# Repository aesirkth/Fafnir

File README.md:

# Fafnir
Propulsion Engine Controller

# Prerequisites
Follow [zephyr getting started guide](https://docs.zephyrproject.org/latest/develop/getting_started/index.html)

# Build 

```bash
cd zephyr-firmware
west update
cd fafnir
west build -b fafnir app --pristine
west flash
```

# Build for native simulation
```bash
docker run -ti -v /Volumes/external/zephyrproject/:/workdir -v /Volumes/external/aesir/Fafnir/zephyr-firmware/:/app ghcr.io/zephyrproject-rtos/zephyr-build:main
cd /app/fafnir
west build -b native_sim/native/64 app --pristine -- -DEXTRA_CONF_FILE=debug.conf
./build/zephyr/zephyr.exe
```
or
```bash
west build -b native_sim/native/64 app -- -DEXTRA_CONF_FILE=debug.conf && ./build/zephyr/zephyr.exe
```

## Using shell in simulation

You can send can messages like this
```bash
uart: ~$ can send can_loopback0 ID DATA
```

For example, running
```bash
uart: ~$ can send can_loopback0 123 0
```
will tell Fafnir to go into state STATE_INIT.

Running 
```bash
uart: ~$ can send can_loopback0 124 0 1
```
will use the override feature to set N2 Valve HIGH.

# CAN message specification to Fafnir

| CAN ID | byte | data                         | type  |
| ------ | ---- | ---------------------------- | ----- |
| 0x123  | 0    | launch sequence number (1-6) | uint8 | (setting states mode)
| 0x124  | 0    | Solenoid ID (1-4)            | uint8 | (override mode)
|        | 1    | 1 == open, 0 == closed       | bool  |

Note that the launch sequence number corresponds to the launch sequence number as given in https://aesir.slab.com/posts/mjollnir-launch-sequence-2juh5ekp

Note that the Solenoid ID corresponds to the solenoid ports on the Fafnir board.
Mjollnir only has two solenoids which correspond to:
```
Solenoid ID 2 => Bypass valve
Solenoid ID 3 => Pilot valve
Solenoid ID 4 => Control vent
```
Solenoid IDs 1 and 4 are not connected and don't do anything.

## CAN acknowledges

| CAN ID | byte | data | meaning |
| ------ | ---- | ------  | -----|
| 0x125  | 0   | 0x01    | Changing state! |
|        | 1   |  \<byte\> |  the state we're changing to |
| 0x125  | 0   | 0x02    | Received valid override command! |
|        | 1   | \<byte\> | The first byte we received  |
|        | 2   |  \<byte\> | The second byte we received  |
| 0x125  | 0   | 0xF0    | Recieved invalid state |
| 0x125  | 0   | 0xF1    | Cannot perform ignition command while attempting ignition. (Protection against double send) |
|  | 1   | \<byte\>    | State command we received |
| 0x125  | 0   | 0xF2    | Invalid state command |
| 0x125  | 0   | 0xF3    | Invalid override command |
| 0x125  | 0   | 0xF4    | Invalid pin given in override command |

The state we're changing to is of type equal to this C `enum`:
```c
typedef enum {
    STATE_IDLE,
    STATE_INIT,
    STATE_FILL,
    STATE_STOP_FILL,
    STATE_UMBILICAL,
    STATE_N2_PRESSURIZATION,
    STATE_IGNITION_1,
    STATE_IGNITION_2,
    STATE_IGNITION_3,
    STATE_IGNITION_4,
    STATE_SAFE,
    STATE_ABORT_BEFORE_COUNTDOWN,
    STATE_ABORT_AFTER_COUNTDOWN
} State_t;
```

Note that this is **NOT** the same as the launch sequence number used in the command above (0x123).

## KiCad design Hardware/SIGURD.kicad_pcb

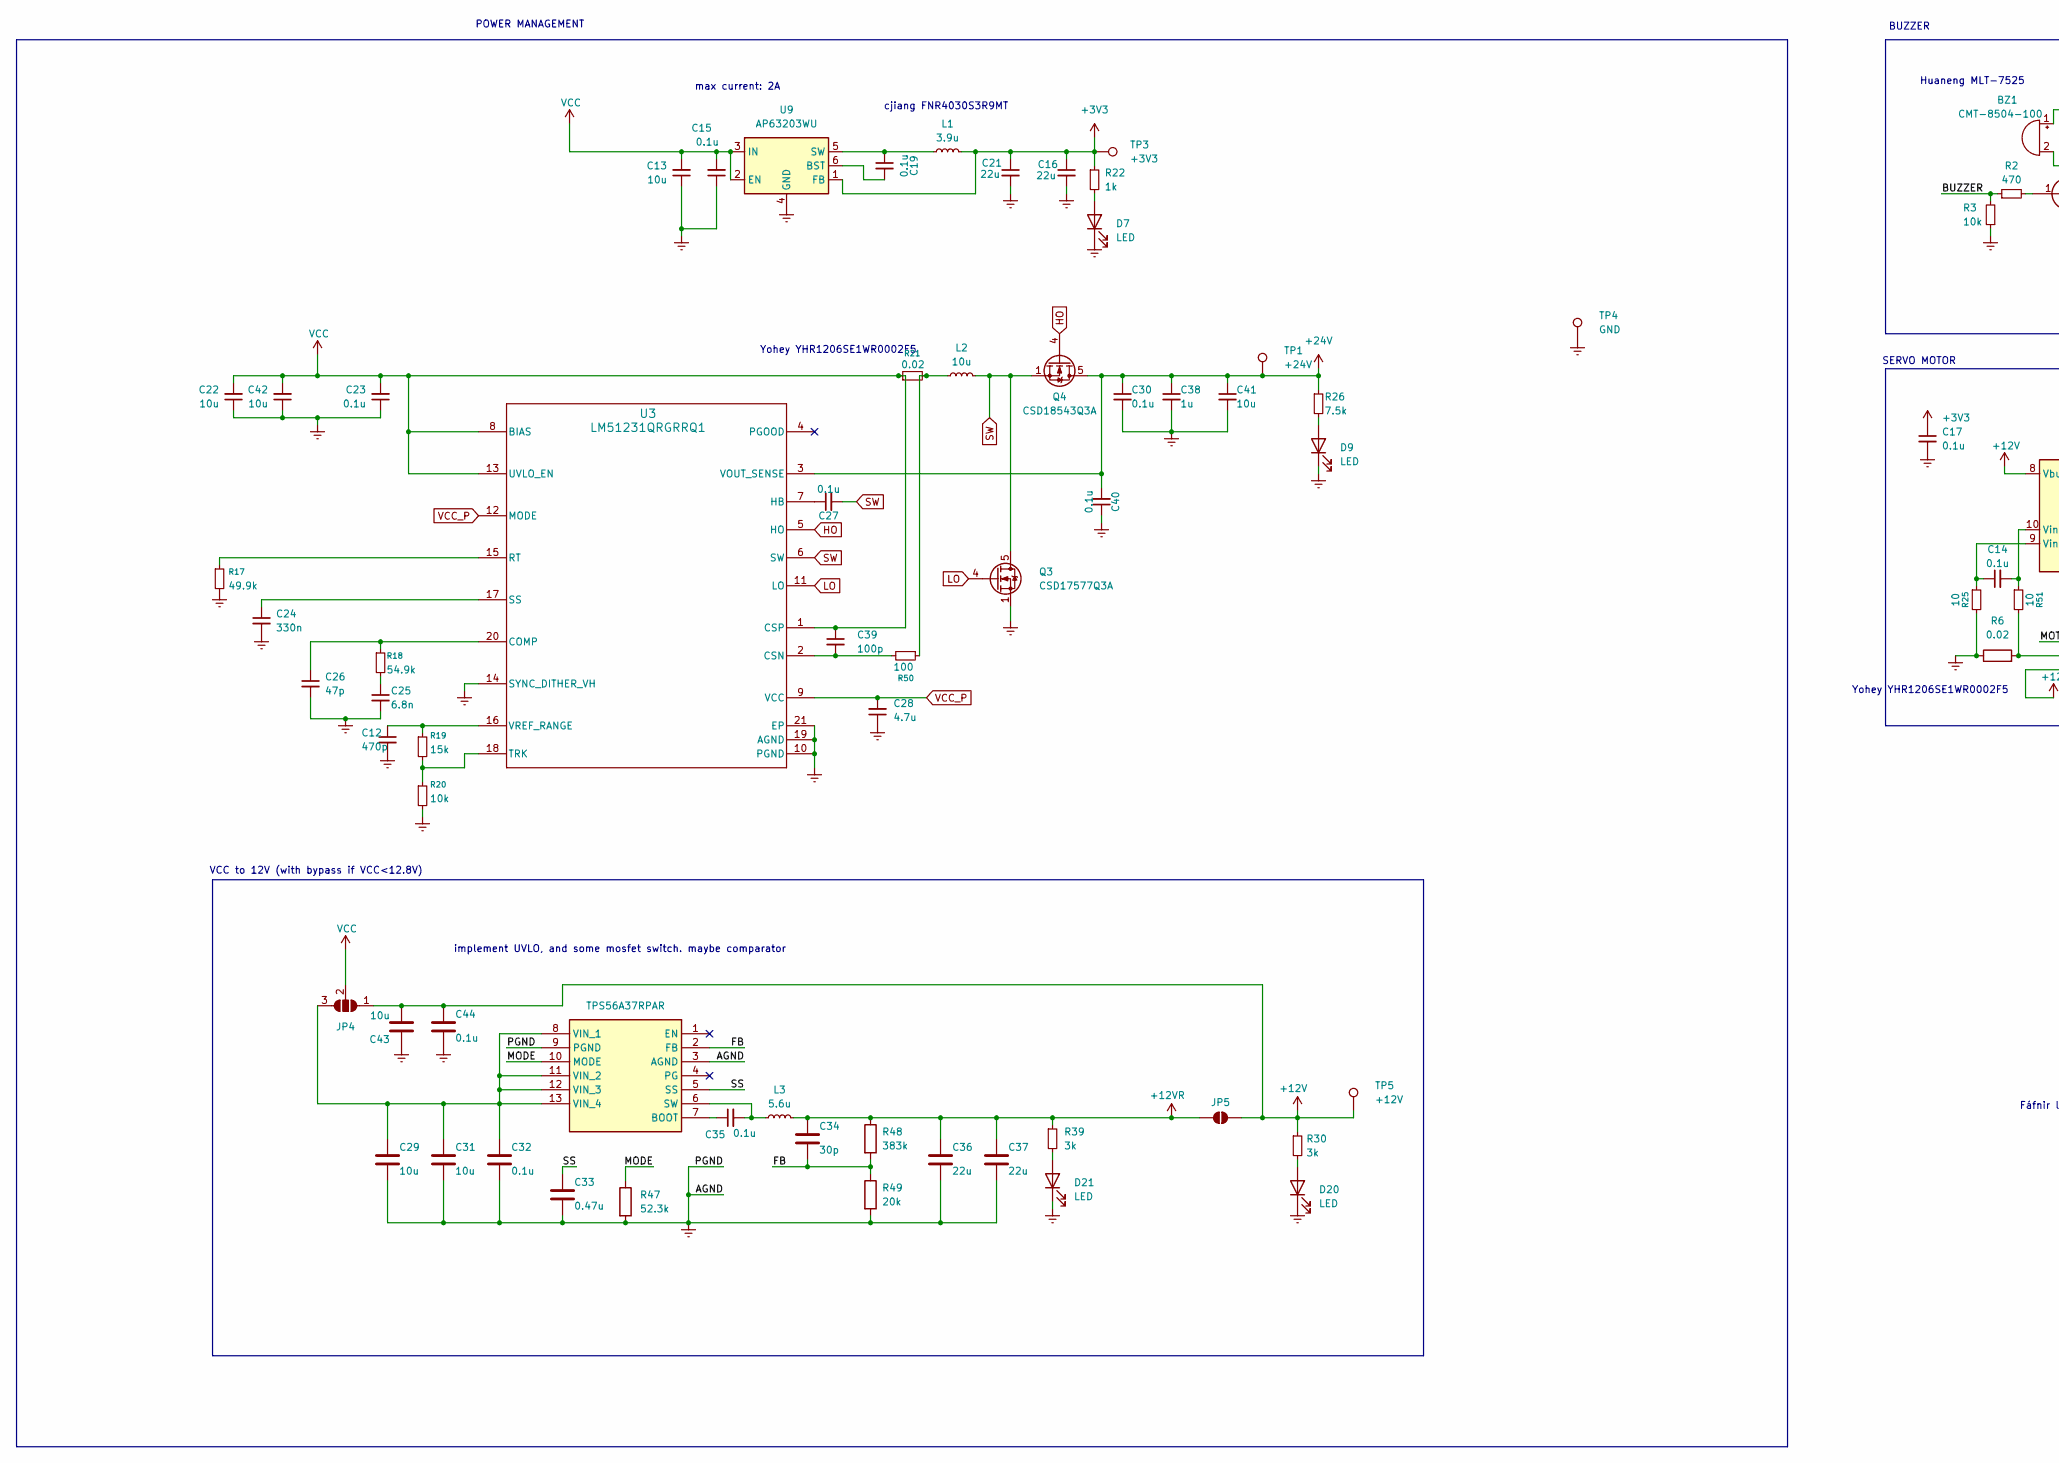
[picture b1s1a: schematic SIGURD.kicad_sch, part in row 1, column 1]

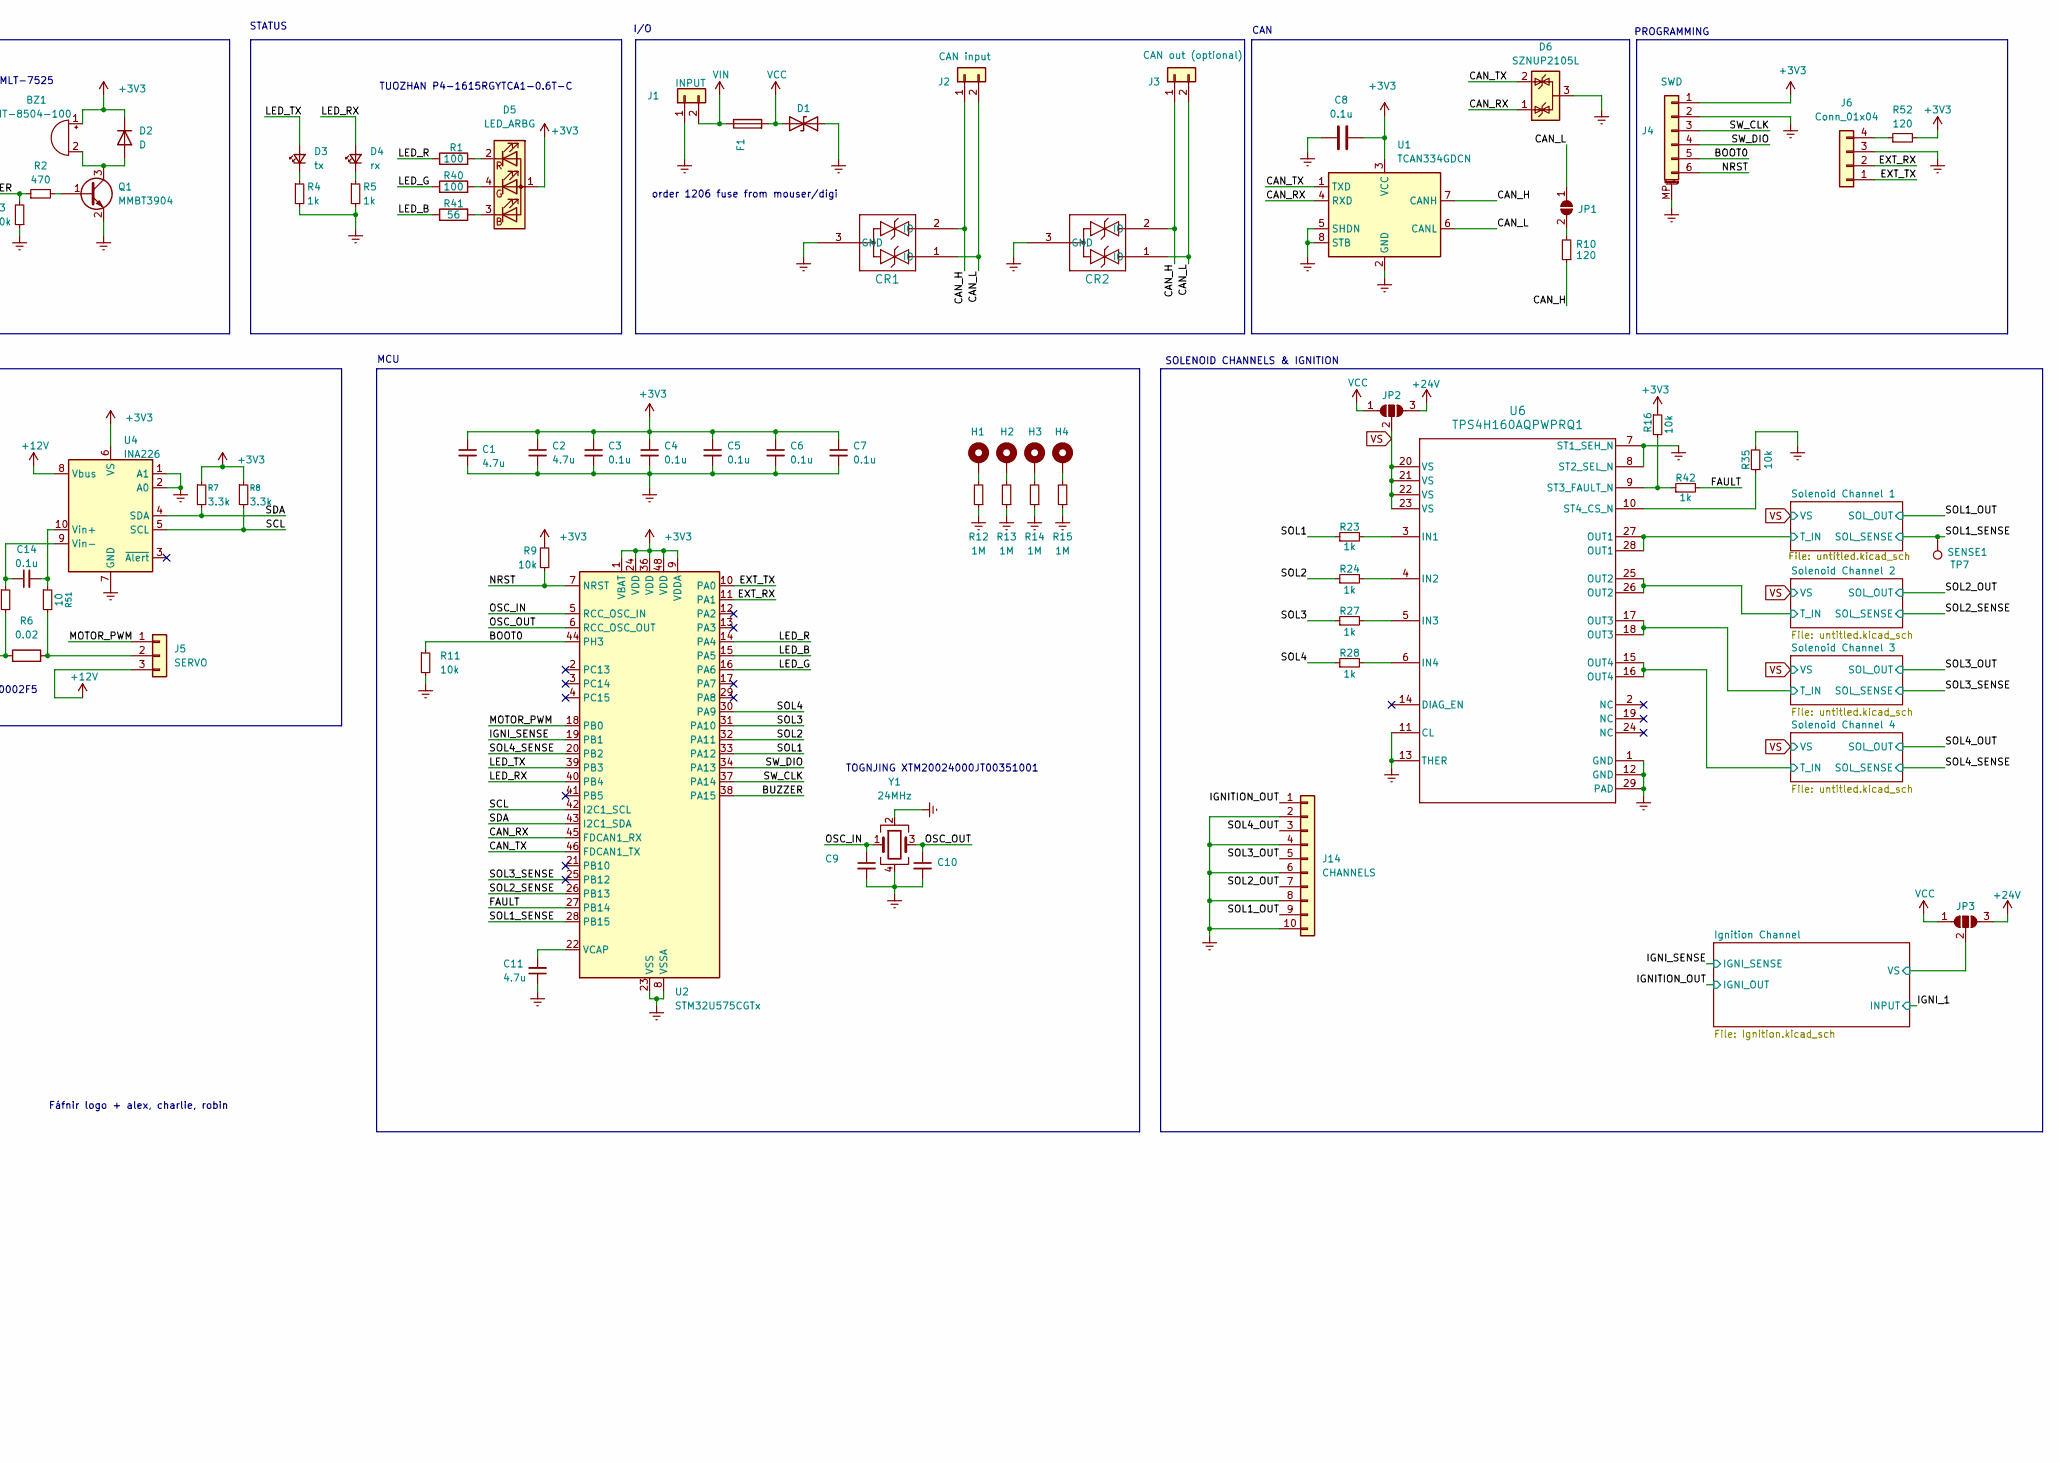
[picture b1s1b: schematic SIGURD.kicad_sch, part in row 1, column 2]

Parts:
BZ1: CMT-8504-100; BUZ-SMD_4P-L7.5-W7.5-P7.59-TL
C1, C2, C11, C28: 4.7u; C_0402_1005Metric
C3, C4, C5, C6, C7, C8, C14, C15, C17, C19, C23, C27, C30, C32, C35, C40, C44: 0.1u; C_0402_1005Metric
C9, C10: 18p; C_0402_1005Metric
C12: 470p; C_0402_1005Metric
C13, C22, C41, C42: 10u; C_0603_1608Metric
C16, C21: 22u; C_0603_1608Metric
C24: 330n; C_0402_1005Metric
C25: 6.8n; C_0402_1005Metric
C26: 47p; C_0402_1005Metric
C29, C31, C43: 10u; C_0805_2012Metric
C33: 0.47u; C_0402_1005Metric
C34: 30p; C_0402_1005Metric
C36, C37: 22u; C_0805_2012Metric
C38: 1u; C_0603_1608Metric
C39: 100p; C_0402_1005Metric
CR1, CR2: ESD2CAN36DBZRQ1; SOT-23-3_DBZ_TEX
D1: D_SOD-123
D2: D; D_SOD-523
D3: tx; D_0603_1608Metric
D4: rx; D_0603_1608Metric
D5: LED_ARBG; LED_Lumex_SML-LX0404SIUPGUSB
D6: SZNUP2105L; SOT-23
D7, D9, D20, D21: LED; D_0603_1608Metric
F1: 15A; Fuse_1206_3216Metric
H1, H2, H3, H4: MountingHole_Pad; MountingHole_3.2mm_M3_Pad_Via
IC3: TPS56A37RPAR; RPA0010A-MFG; Mouser Part Number 595-TPS56A37RPAR
J1: INPUT; AMASS_XT30PW-F_1x02_P2.50mm_Horizontal
J2: CAN input; JST_XH_B2B-XH-A_1x02_P2.50mm_Vertical
J3: CAN out (optional); JST_XH_B2B-XH-A_1x02_P2.50mm_Vertical
J4: SWD; JST_SH_SM06B-SRSS-TB_1x06-1MP_P1.00mm_Horizontal
J5: SERVO; CONN_1727023_PXC
J6: Conn_01x04; PinSocket_1x04_P1.27mm_Vertical
J14: CHANNELS; CONN10_1935242_PXC
JP1: SolderJumper_2_Open; SolderJumper-2_P1.3mm_Open_TrianglePad1.0x1.5mm
JP2, JP3: SolderJumper_3_Open; SolderJumper-3_P2.0mm_Open_TrianglePad1.0x1.5mm_NumberLabels
JP4: SolderJumper_3_Open; SolderJumper-3_P1.3mm_Open_Pad1.0x1.5mm_NumberLabels
JP5: SolderJumper_2_Open; SolderJumper-2_P1.3mm_Open_Pad1.0x1.5mm
L1: 3.9u; L_Changjiang_FNR4030S
L2: 10u; IND-SMD_L7.0-W6.6_FAUL06XX
L3: 5.6u; IND-SMD_L6.6-W6.4
Q1: MMBT3904; SOT-23
Q3: CSD17577Q3A; VSON-8_3.3x3.3mm_P0.65mm_NexFET
Q4: CSD18543Q3A; VSON-8_3.3x3.3mm_P0.65mm_NexFET
R1, R40, R50: 100; R_0402_1005Metric
R2: 470; R_0603_1608Metric_Pad0.98x0.95mm_HandSolder
R3: 10k; R_0603_1608Metric_Pad0.98x0.95mm_HandSolder
R4, R5, R22: 1k; R_0603_1608Metric
R6, R21: 0.02; R_2512_6332Metric
R7, R8: 3.3k; R_0402_1005Metric
R9, R11, R16, R20, R35: 10k; R_0402_1005Metric
R10: 120; R_0603_1608Metric_Pad0.98x0.95mm_HandSolder
R12, R13, R14, R15: 1M; R_0603_1608Metric
R17: 49.9k; C_0402_1005Metric
R18: 54.9k; R_0402_1005Metric
R19: 15k; R_0402_1005Metric
R23, R24, R27, R28, R42: 1k; R_0402_1005Metric
R25, R51: 10; R_0402_1005Metric
R26: 7.5k; R_0603_1608Metric
R30, R39: 3k; R_0603_1608Metric
R41: 56; R_0402_1005Metric
R47: 52.3k; R_0402_1005Metric
R48: 383k; R_0402_1005Metric
R49: 20k; R_0402_1005Metric
R52: 120; R_0402_1005Metric
TP1: +24V; TestPoint_Pad_D2.0mm
TP3: +3V3; TestPoint_Pad_D2.0mm
TP4: GND; TestPoint_Pad_D2.0mm
TP5: +12V; TestPoint_Pad_D2.0mm
TP7: SENSE1; TestPoint_Pad_D2.0mm
U1: TCAN334GDCN; TSOT-23-8
U2: STM32U575CGTx; LQFP-48_7x7mm_P0.5mm
U3: LM51231QRGRRQ1; RGR0020C-MFG
U4: INA226; VSSOP-10_3x3mm_P0.5mm
U6: TPS4H160AQPWPRQ1; PWP0028C_N
U9: AP63203WU; TSOT-23-6
Y1: 24MHz; Crystal_SMD_2016-4Pin_2.0x1.6mm

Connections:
+3V3: BZ1.1 (-), C1.1, C2.1, C3.1, C4.1, C5.1, C6.1, C7.1, C8.2, C16.1, C17.1, C21.1, D2.1 (K), D5.1 (A), J4.1, L1.2, R7.1, R8.1, R9.2, R16.1, R22.1, R52.2, TP3.1, U1.3 (VCC), U2.1 (VBAT), U2.9 (VDDA), U2.24 (VDD), U2.36 (VDD), U2.48 (VDD), U4.6 (VS), U9.1 (FB)
+12V: C43.1, C44.2, J5.3, JP4.1 (A), JP5.2 (B), R30.1, TP5.1, U4.8 (Vbus)
+12VR: C34.2, C36.2, C37.2, JP5.1 (A), L3.2, R39.1, R48.1
+24V: C30.1, C38.1, C40.2, C41.1, JP2.3 (B), JP3.3 (B), Q4.5 (D), R26.1, TP1.1, U3.3 (VOUT_SENSE)
/BOOT0: J4.5, R11.1, U2.44 (PH3)
/BUZZER: R2.1, R3.2, U2.38 (PA15)
/CAN_H: CR1.2 (IO), CR2.2 (IO), J2.1, J3.1, R10.1, U1.7 (CANH)
/CAN_L: CR1.1 (IO), CR2.1 (IO), J2.2, J3.2, JP1.1 (A), U1.6 (CANL)
/CAN_RX: D6.1 (K), U1.4 (RXD), U2.45 (FDCAN1_RX)
/CAN_TX: D6.2 (K), U1.1 (TXD), U2.46 (FDCAN1_TX)
/EXT_RX: J6.2, U2.11 (PA1)
/EXT_TX: J6.1, U2.10 (PA0)
/FAULT: R42.2, U2.27 (PB14)
/FB: C34.1, IC3.2 (FB), R48.2, R49.1
/IGNITION_OUT: J14.1; also elsewhere on the board
/IGNI_SENSE: U2.19 (PB1); also elsewhere on the board
/Ignition Channel/VS: JP3.2 (C); also elsewhere on the board
/LED_B: R41.1, U2.15 (PA5)
/LED_G: R40.1, U2.16 (PA6)
/LED_R: R1.1, U2.14 (PA4)
/LED_RX: D4.2 (A), U2.40 (PB4)
/LED_TX: D3.2 (A), U2.39 (PB3)
/MODE: IC3.10 (MODE), R47.1
/MOTOR_PWM: J5.1, U2.18 (PB0)
/NRST: J4.6, R9.1, U2.7 (NRST)
/OSC_IN: C9.1, U2.5 (RCC_OSC_IN), Y1.1
/OSC_OUT: C10.1, U2.6 (RCC_OSC_OUT), Y1.3
/SCL: R8.2, U2.42 (I2C1_SCL), U4.5 (SCL)
/SDA: R7.2, U2.43 (I2C1_SDA), U4.4 (SDA)
/SOL1: R23.1, U2.33 (PA12)
/SOL1_OUT: J14.9; also elsewhere on the board
/SOL1_SENSE: TP7.1, U2.28 (PB15); also elsewhere on the board
/SOL2: R24.1, U2.32 (PA11)
/SOL2_OUT: J14.7; also elsewhere on the board
/SOL2_SENSE: U2.26 (PB13); also elsewhere on the board
/SOL3: R27.1, U2.31 (PA10)
/SOL3_OUT: J14.5; also elsewhere on the board
/SOL3_SENSE: U2.25 (PB12); also elsewhere on the board
/SOL4: R28.1, U2.30 (PA9)
/SOL4_OUT: J14.3; also elsewhere on the board
/SOL4_SENSE: U2.20 (PB2); also elsewhere on the board
/SS: C33.2, IC3.5 (SS)
/SW_CLK: J4.3, U2.37 (PA14)
/SW_DIO: J4.4, U2.34 (PA13)
/Solenoid Channel 1/T_IN: U6.27 (OUT1), U6.28 (OUT1); also elsewhere on the board
/Solenoid Channel 2/T_IN: U6.25 (OUT2), U6.26 (OUT2); also elsewhere on the board
/Solenoid Channel 3/T_IN: U6.17 (OUT3), U6.18 (OUT3); also elsewhere on the board
/Solenoid Channel 4/T_IN: U6.15 (OUT4), U6.16 (OUT4); also elsewhere on the board
Earth: C1.2, C2.2, C3.2, C4.2, C5.2, C6.2, C7.2, C8.1, C9.2, C10.2, C11.1, C12.2, C13.1, C15.1, C16.2, C17.2, C21.2, C22.1, C23.1, C24.2, C25.2, C26.2, C28.1, C29.1, C30.2, C31.1, C32.1, C33.1, C36.1, C37.1, C38.2, C40.1, C41.2, C42.1, C43.2, C44.1, CR1.3 (GND), CR2.3 (GND), D1.1 (A1), D6.3 (A), D7.1 (K), D9.1 (K), D20.1 (K), D21.1 (K), IC3.3 (AGND), IC3.9 (PGND), J1.1, J4.2, J4.MP (MountPin), J6.3, J14.2, J14.4, J14.6, J14.8, J14.10, Q1.2 (E), Q3.1 (S), Q3.2 (S), Q3.3 (S), R3.1, R4.2, R5.2, R6.1, R11.2, R12.1, R13.1, R14.1, R15.1, R17.2, R20.2, R25.2, R35.2, R47.2, R49.2, TP4.1, U1.2 (GND), U1.5 (SHDN), U1.8 (STB), U2.8 (VSSA), U2.23 (VSS), U2.35 (VSS), U2.47 (VSS), U3.10 (PGND), U3.14 (SYNC_DITHER_VH), U3.19 (AGND), U3.21 (EP), U3.22, U3.23, U3.24, U3.25, U3.26, U4.1 (A1), U4.2 (A0), U4.7 (GND), U6.1 (GND), U6.7 (ST1_SEH_N), U6.8 (ST2_SEL_N), U6.11 (CL), U6.12 (GND), U6.13 (THER), U6.29 (PAD), U6.V, U9.4 (GND), Y1.2, Y1.4; also elsewhere on the board
HO: Q4.4 (G), U3.5 (HO)
LO: Q3.4 (G), U3.11 (LO)
unnamed: BZ1.2 (+), D2.2 (A), Q1.3 (C)
unnamed: C25.1, R18.2
unnamed: D3.1 (K), R4.1
unnamed: D4.1 (K), R5.1
unnamed: D5.3 (BK), R41.2
unnamed: D5.4 (GK), R40.2
unnamed: D5.2 (RK), R1.2
unnamed: D7.2 (A), R22.2
unnamed: D9.2 (A), R26.2
unnamed: D20.2 (A), R30.2
unnamed: D21.2 (A), R39.2
unnamed: H1.1, R12.2
unnamed: H2.1, R13.2
unnamed: H3.1, R14.2
unnamed: H4.1, R15.2
unnamed: C35.1, IC3.7 (BOOT)
unnamed: C35.2, IC3.6 (SW), L3.1
unnamed: C29.2, C31.2, C32.2, IC3.8 (VIN_1), IC3.11 (VIN_2), IC3.12 (VIN_3), IC3.13 (VIN_4), JP4.3 (B)
unnamed: J5.2, R6.2, R51.2
unnamed: J6.4, R52.1
unnamed: JP1.2 (B), R10.2
unnamed: L2.1, R21.2, R50.1
unnamed: Q1.1 (B), R2.2
unnamed: C11.2, U2.22 (VCAP)
unnamed: C26.1, R18.1, U3.20 (COMP)
unnamed: C39.2, R50.2, U3.2 (CSN)
unnamed: C27.1, U3.7 (HB)
unnamed: R17.1, U3.15 (RT)
unnamed: C24.1, U3.17 (SS)
unnamed: R19.2, R20.1, U3.18 (TRK)
unnamed: C12.1, R19.1, U3.16 (VREF_RANGE)
unnamed: C14.2, R51.1, U4.10 (Vin+)
unnamed: C14.1, R25.1, U4.9 (Vin-)
unnamed: R23.2, U6.3 (IN1)
unnamed: R24.2, U6.4 (IN2)
unnamed: R27.2, U6.5 (IN3)
unnamed: R28.2, U6.6 (IN4)
unnamed: R16.2, R42.1, U6.9 (ST3_FAULT_N)
unnamed: R35.1, U6.10 (ST4_CS_N)
unnamed: C19.2, U9.6 (BST)
unnamed: C19.1, L1.1, U9.5 (SW)
SW: C27.2, L2.2, Q3.5 (D), Q4.1 (S), Q4.2 (S), Q4.3 (S), U3.6 (SW)
VCC: C13.2, C15.2, C22.2, C23.2, C39.1, C42.2, D1.2 (A2), F1.2, JP2.1 (A), JP3.1 (A), JP4.2 (C), R21.1, U3.1 (CSP), U3.8 (BIAS), U3.13 (UVLO_EN), U9.2 (EN), U9.3 (IN)
VCC_P: C28.2, U3.9 (VCC), U3.12 (MODE)
VIN: F1.1, J1.2
VS: JP2.2 (C), U6.20 (VS), U6.21 (VS), U6.22 (VS), U6.23 (VS); also elsewhere on the board

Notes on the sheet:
BUZZER
VCC to 12V (with bypass if VCC<12.8V)
I/O
SOLENOID CHANNELS & IGNITION
Yohey YHR1206SE1WR0002F5
Huaneng MLT-7525
Fáfnir logo + alex, charlie, robin
PROGRAMMING
cjiang FNR4030S3R9MT
max current: 2A
implement UVLO, and some mosfet switch. maybe comparator
order 1206 fuse from mouser/digi
CAN
POWER MANAGEMENT
TOGNJING XTM20024000JT00351001
SERVO MOTOR
TUOZHAN P4-1615RGYTCA1-0.6T-C
MCU
STATUS

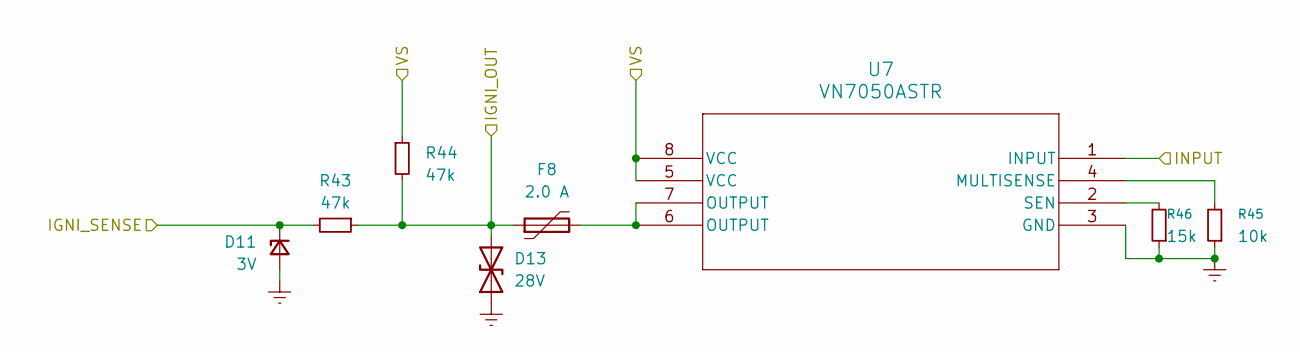
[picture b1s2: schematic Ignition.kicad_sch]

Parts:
D11: 3V; D_SOD-323_HandSoldering
D13: 28V; D_0603_1608Metric_Pad1.05x0.95mm_HandSolder
F8: 2.0 A; Fuse_1812_4532Metric
R43, R44: 47k; R_0603_1608Metric_Pad0.98x0.95mm_HandSolder
R45: 10k; R_0201_0603Metric
R46: 15k; R_0201_0603Metric
U7: VN7050ASTR; SOIC_050ASTR_STM

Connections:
/IGNITION_OUT: D13.2 (A2), F8.1, R43.1, R44.2; also elsewhere on the board
/IGNI_1: U7.1 (INPUT)
/IGNI_SENSE: D11.1 (K), R43.2; also elsewhere on the board
/Ignition Channel/VS: R44.1, U7.5 (VCC), U7.8 (VCC); also elsewhere on the board
Earth: D11.2 (A), D13.1 (A1), R45.1, R46.1, U7.3 (GND); also elsewhere on the board
unnamed: F8.2, U7.6 (OUTPUT), U7.7 (OUTPUT)
unnamed: R45.2, U7.4 (MULTISENSE)
unnamed: R46.2, U7.2 (SEN)

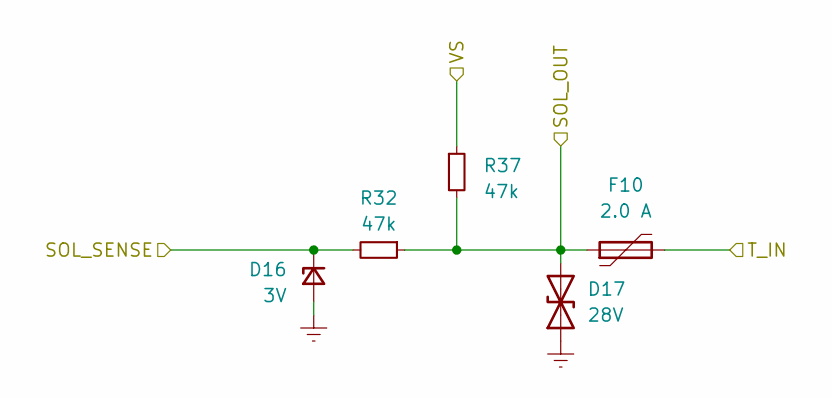
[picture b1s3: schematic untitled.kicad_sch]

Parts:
D16: 3V; D_SOD-323_HandSoldering
D17: 28V; D_0603_1608Metric_Pad1.05x0.95mm_HandSolder
F10: 2.0 A; Fuse_1812_4532Metric
R32, R37: 47k; R_0603_1608Metric_Pad0.98x0.95mm_HandSolder

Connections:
/SOL3_OUT: D17.2 (A2), F10.1, R32.1, R37.2; also elsewhere on the board
/SOL3_SENSE: D16.1 (K), R32.2; also elsewhere on the board
/Solenoid Channel 3/T_IN: F10.2; also elsewhere on the board
Earth: D16.2 (A), D17.1 (A1); also elsewhere on the board
VS: R37.1; also elsewhere on the board

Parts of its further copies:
D10, D14, D18: 3V; D_SOD-323_HandSoldering
R29, R31, R33, R34, R36, R38: 47k; R_0603_1608Metric_Pad0.98x0.95mm_HandSolder

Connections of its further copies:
/SOL1_OUT: R29.1, R34.2; also elsewhere on the board
/SOL1_SENSE: D10.1 (K), R29.2; also elsewhere on the board
/SOL2_OUT: R31.1, R36.2; also elsewhere on the board
/SOL2_SENSE: D14.1 (K), R31.2; also elsewhere on the board
/SOL4_OUT: R33.1, R38.2; also elsewhere on the board
/SOL4_SENSE: D18.1 (K), R33.2; also elsewhere on the board
Earth: D10.2 (A), D14.2 (A), D18.2 (A); also elsewhere on the board
VS: R34.1, R36.1, R38.1; also elsewhere on the board

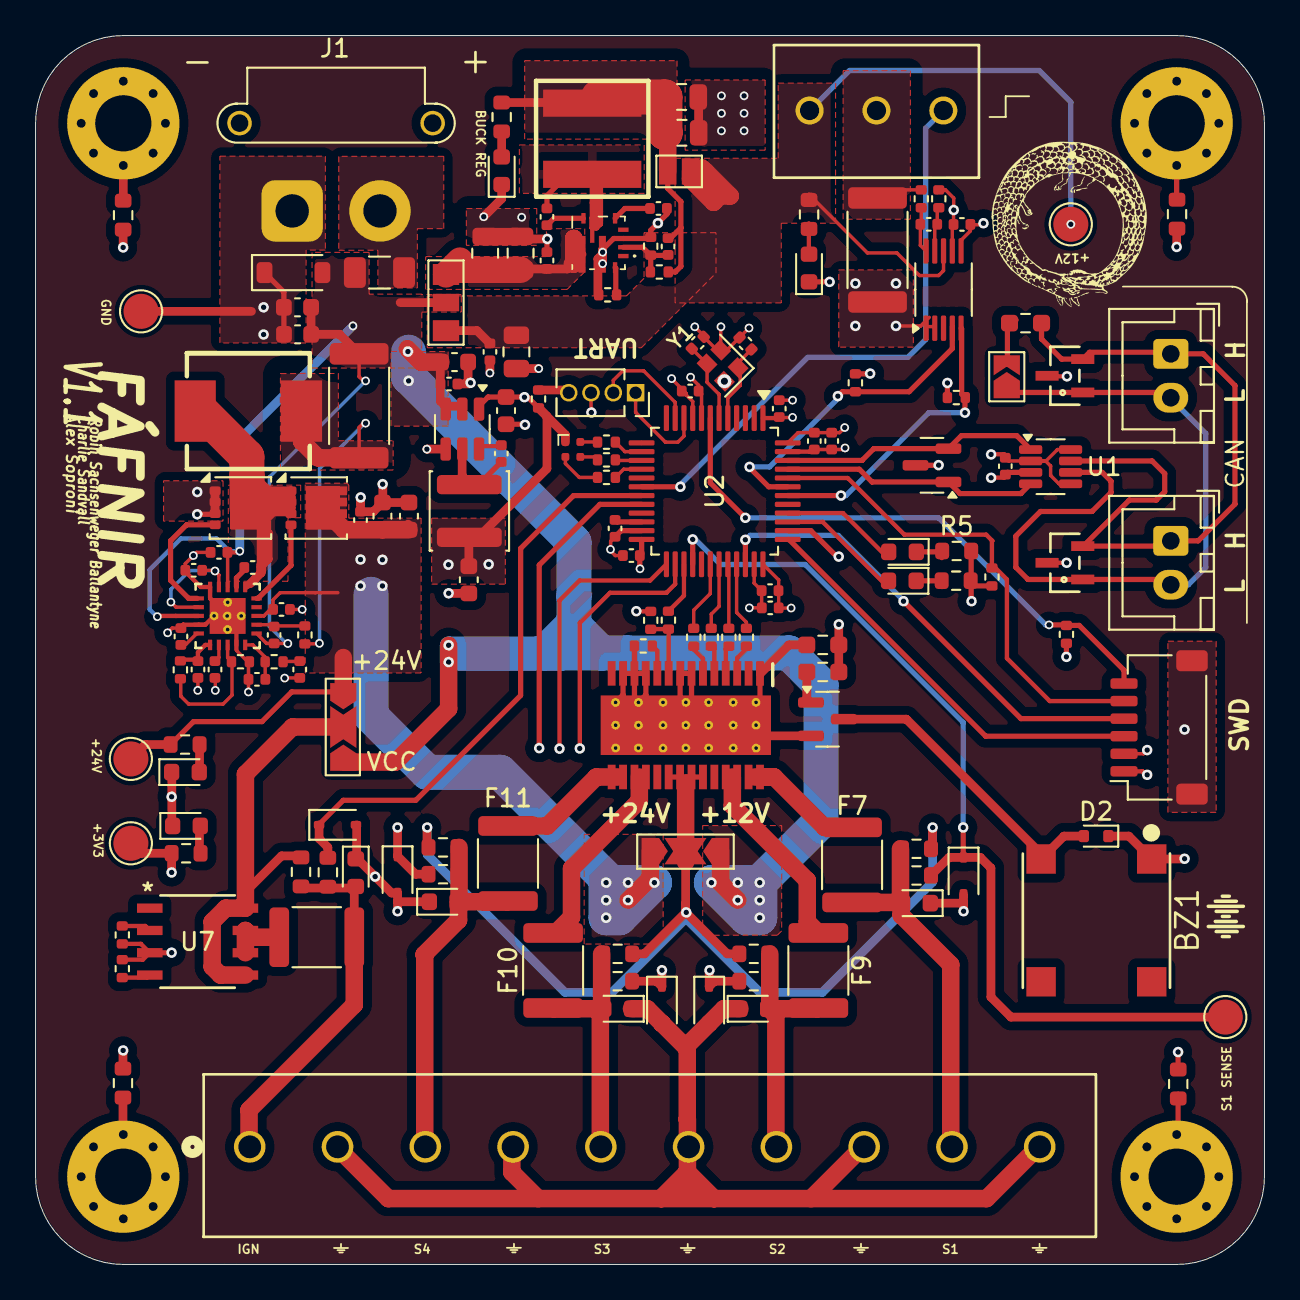
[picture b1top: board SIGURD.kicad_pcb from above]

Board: 4 copper layers, 70.0 x 70.0 mm, 159 parts (0 on the bottom side), 100 nets.

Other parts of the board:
D12, D15, D19: D_0603_1608Metric
F7, F9, F11: 1.0A; Fuse_1812_4532Metric

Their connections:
/SOL1_OUT: D12.2 (A2), F7.1; also elsewhere on the board
/SOL2_OUT: D15.2 (A2), F9.1; also elsewhere on the board
/SOL4_OUT: D19.2 (A2), F11.1; also elsewhere on the board
/Solenoid Channel 1/T_IN: F7.2; also elsewhere on the board
/Solenoid Channel 2/T_IN: F9.2; also elsewhere on the board
/Solenoid Channel 4/T_IN: F11.2; also elsewhere on the board
Earth: D12.1 (A1), D15.1 (A1), D19.1 (A1); also elsewhere on the board

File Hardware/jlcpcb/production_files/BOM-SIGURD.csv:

Comment,Designator,Footprint,LCSC,Quantity
54.9k,R18,R_0402_1005Metric,C11626,1
1k,"R23,R24,R27,R28,R42",R_0402_1005Metric,C11702,5
100p,C39,C_0402_1005Metric,C1546,1
18p,"C10,C9",C_0402_1005Metric,C1549,2
47p,C26,C_0402_1005Metric,C1567,1
30p,C34,C_0402_1005Metric,C1570,1
1u,C38,C_0603_1608Metric,C15849,1
10u,"C29,C31,C43",C_0805_2012Metric,C15850,3
3.9u,L1,L_Changjiang_FNR4030S,C167872,1
49.9k,R17,C_0402_1005Metric,C173335,1
3V,"D10,D11,D14,D16,D18",D_SOD-323,C19077437,5
LED,D7,D_0603_1608Metric,C19171301,1
10u,"C13,C22,C41,C42",C_0603_1608Metric,C194427,4
CSD17577Q3A,Q3,VSON-8_3.3x3.3mm_P0.65mm_NexFET,C201632,1
MMBT3904,Q1,SOT-23,C20526,1
1.0A,"F10,F11,F7,F8,F9",Fuse_1812_4532Metric,C20997,5
1k,"R22,R4,R5",R_0603_1608Metric,C21190,3
TPS56A37RPAR,IC3,RPA0010A-MFG,C22392669,1
52.3k,R47,R_0402_1005Metric,C227130,1
120,R10,R_0603_1608Metric_Pad0.98x0.95mm_HandSolder,C22787,1
rx,D4,D_0603_1608Metric,C2286,1
LED,D9,D_0603_1608Metric,C2288,1
LED,"D21,D3",D_0603_1608Metric,C2290,2
1M,"R12,R13,R14,R15",R_0603_1608Metric,C22935,4
3k,"R30,R39",R_0603_1608Metric,C22978,2
SZNUP2105L,D6,SOT-23,C23083861,1
470,R2,R_0603_1608Metric_Pad0.98x0.95mm_HandSolder,C23179,1
D,D2,D_SOD-523,C232841,1
4.7u,"C1,C11,C2,C28",C_0402_1005Metric,C23733,4
100,R50,R_0402_1005Metric,C25076,1
10,"R25,R51",R_0402_1005Metric,C25077,2
120,R52,R_0402_1005Metric,C25079,1
10k,"R11,R16,R20,R35,R45,R9",R_0402_1005Metric,C25744,6
15k,"R19,R46",R_0402_1005Metric,C25756,2
20k,R49,R_0402_1005Metric,C25765,1
10k,R3,R_0603_1608Metric_Pad0.98x0.95mm_HandSolder,C25804,1
3.3k,"R7,R8",R_0402_1005Metric,C25890,2
INA226,U4,VSSOP-10_3x3mm_P0.5mm,C2653870,1
TCAN334GDCN,U1,TSOT-23-8,C2671013,1
ESD2CAN36DBZRQ1,"CR1,CR2",SOT-23-3_DBZ_TEX,C284078,2
0.1u,"C14,C15,C17,C19,C23,C27,C3,C30,C32,C35,C4,C40,C44,C5,C6,C7,C8",C_0402_1005Metric,C307331,17
47k,"R29,R31,R32,R33,R34,R36,R37,R38,R43,R44",R_0603_1608Metric,C307918,10
~,"D12,D13,D15,D17,D19",D_0603_1608Metric,C328933,5
24MHz,Y1,Crystal_SMD_2016-4Pin_2.0x1.6mm,C37635323,1
~,D1,D_SOD-123,C435489,1
7.5k,R26,R_0603_1608Metric,C441926,1
VN7050ASTR,U7,SOIC_050ASTR_STM,C443993,1
22u,"C36,C37",C_0805_2012Metric,C45783,2
383k,R48,R_0402_1005Metric,C45993,1
TPS4H160AQPWPRQ1,U6,PWP0028C_N,C485918,1
0.02,"R21,R6",R_2512_6332Metric,C49164694,2
10u,L2,IND-SMD_L7.0-W6.6_FAUL06XX,C5298253,1
5.6u,L3,IND-SMD_L6.6-W6.4,C5378545,1
330n,C24,C_0402_1005Metric,C5448882,1
22u,"C16,C21",C_0603_1608Metric,C59461,2
LM51231QRGRRQ1,U3,RGR0020C-MFG,C6286802,1
470p,C12,C_0402_1005Metric,C76971,1
AP63203WU,U9,TSOT-23-6,C780769,1
CSD18543Q3A,Q4,VSON-8_3.3x3.3mm_P0.65mm_NexFET,C840100,1
0.47u,C33,C_0402_1005Metric,C92361,1
6.8n,C25,C_0402_1005Metric,C93654,1
CMT-8504-100,BZ1,BUZ-SMD_4P-L7.5-W7.5-P7.59-TL,C95299,1
LED,D20,D_0603_1608Metric,C965807,1

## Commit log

2025-10-11 Added hardware and firmware folder
2025-10-27 Implemented State machine logic
2025-10-30 added zephyr firmware folder
2025-10-30 blinky builds
2025-10-30 deleted some things
2025-10-30 blinky was flashed
2025-10-30 pwm but it does not work
2025-11-01 Fixed the rest of the cubeIDE code, ready to be implemented into Zephyr
2025-11-02 some changes pwm still does not work
2025-11-02 pwm test now works!!!
2025-11-02 changed name of example application
2025-11-02 added return; for invalid angles
2025-11-02 deleted build directory
2025-11-02 Added bare minimum dts for HIL
2025-11-02 servoZero and servoRotate works
2025-11-02 not working sensing
2025-11-02 removed the cubeIDE remnant from the old code
2025-11-02 builds now; fixed variable not declared
2025-11-02 added module.yml file back into repo
2025-11-12 Fáfnir V1.1 redesign
2025-11-13 dummy CAN receiving but not tested on actual board
2025-11-13 can test
2025-11-13 logging update
2025-11-24 fafnir redesign :)
2025-11-25 native sim
2025-11-25 new states and dt
2025-11-25 added stuffs
2025-11-25 more random stuffs
2025-11-25 some code for the ignition sequence. compiled and working
2025-11-27 emulated gpio pins can be controlled and displayed using shell commands
2025-12-03 launch sequence
2025-12-03 enable CAN loopback only during simulation
2025-12-09 added dts for new fafnir
2025-12-09 device tree fafnir builds again
2025-12-09 added blinky test
2025-12-09 testing servo motor not working
2025-12-09 sending CAN works
2025-12-09 receiving CAN messages works on blinky
2025-12-16 changed pin outs and fixed isStateBeforeCountdown
2025-12-16 removed todo
2026-01-19 reordered CAN override pins so that they match the text on the PCB
2026-01-21 error checking
2026-02-19 README containing Fafnir CAN commands specification
2026-02-25 Add Solenoid ID 4 information to README
2026-03-02 newest changes from native-sim branch
2026-03-02 native sim board file
2026-03-02 cleaning out useless files
2026-03-22 acknowledges
